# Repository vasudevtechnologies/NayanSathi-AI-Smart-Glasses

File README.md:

# NayanSathi-AI-Smart-Glasses
🕶️ NayanSathi — AI Smart Glasses for the Visually Impaired NayanSathi is an AI-powered wearable assistive system designed to help visually impaired individuals navigate and understand their surroundings in real time. Built using Raspberry Pi 4, ESP32-CAM, YOLOv11, and Edge AI technologies, the smart glasses detect nearby objects

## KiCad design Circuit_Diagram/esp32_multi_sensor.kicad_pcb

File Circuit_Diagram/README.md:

# ⚡ Circuit_Diagram

This folder contains all circuit schematics and PCB design files for **NayanSathi — AI Smart Glasses**.

## Contents
- `esp32_multi_sensor.kicad_pcb` — Main KiCad PCB design
- `schematic.pdf` — Printable full circuit schematic
- `wiring_diagram.png` — Complete wiring connection diagram
- `power_circuit.png` — Solar + battery power circuit
- `pcb_gerber/` — Gerber files for PCB manufacturing

## Power Circuit

```
☀️ Solar Panel (5V, 1W)
         │
         ▼
   ┌─────────────┐
   │   TP4056    │  ← Charge Controller (overcharge protected)
   │   Module    │
   └──────┬──────┘
          │
          ▼
   Li-Po Battery (3.7V, 3000mAh)
          │
          ▼
   ┌─────────────┐
   │   MT3608    │  ← Boost Converter (3.7V → 5V)
   │   Boost     │
   └──────┬──────┘
          │
     ┌────┴────┐
     ▼         ▼
Raspberry Pi 4  ESP32-CAM
  (USB-C 5V)   (5V Pin)
```

## Pin Connections

| From | Pin | To | Pin | Signal |
|---|---|---|---|---|
| ESP32-CAM | GPIO 1 (TX) | Raspberry Pi | GPIO 15 (RX) | UART |
| ESP32-CAM | 5V | MT3608 OUT | 5V | Power |
| ESP32-CAM | GND | Common GND | GND | Ground |
| Solar Panel | + | TP4056 | IN+ | 5V Solar Input |
| Solar Panel | - | TP4056 | IN- | Ground |
| TP4056 | BAT+ | Li-Po | + | Battery Charge |
| Li-Po | + | MT3608 | IN+ | 3.7V Input |
| MT3608 | OUT+ | Pi USB-C | + | 5V Output |
| Voltage Divider | OUT | Pi | GPIO ADC | Battery % |

## PCB Features (KiCad Design)
- ESP32-CAM mounting pads with castellated holes
- TP4056 solar charge controller footprint
- MT3608 boost converter section
- Voltage divider circuit (100kΩ + 100kΩ) for battery ADC monitoring
- I2C header (SDA/SCL) for optional IMU / barometer sensor
- Push button (GPIO 17) for mode switching
- 3x LED indicators: Power (Green), Bluetooth (Blue), Detection (Cyan)
- Magnetic pogo-pin pads for solar panel connector

## PCB Dimensions
- Size: ~45mm × 30mm (fits inside glasses frame)
- Layers: 2-layer PCB
- Thickness: 1.6mm standard FR4

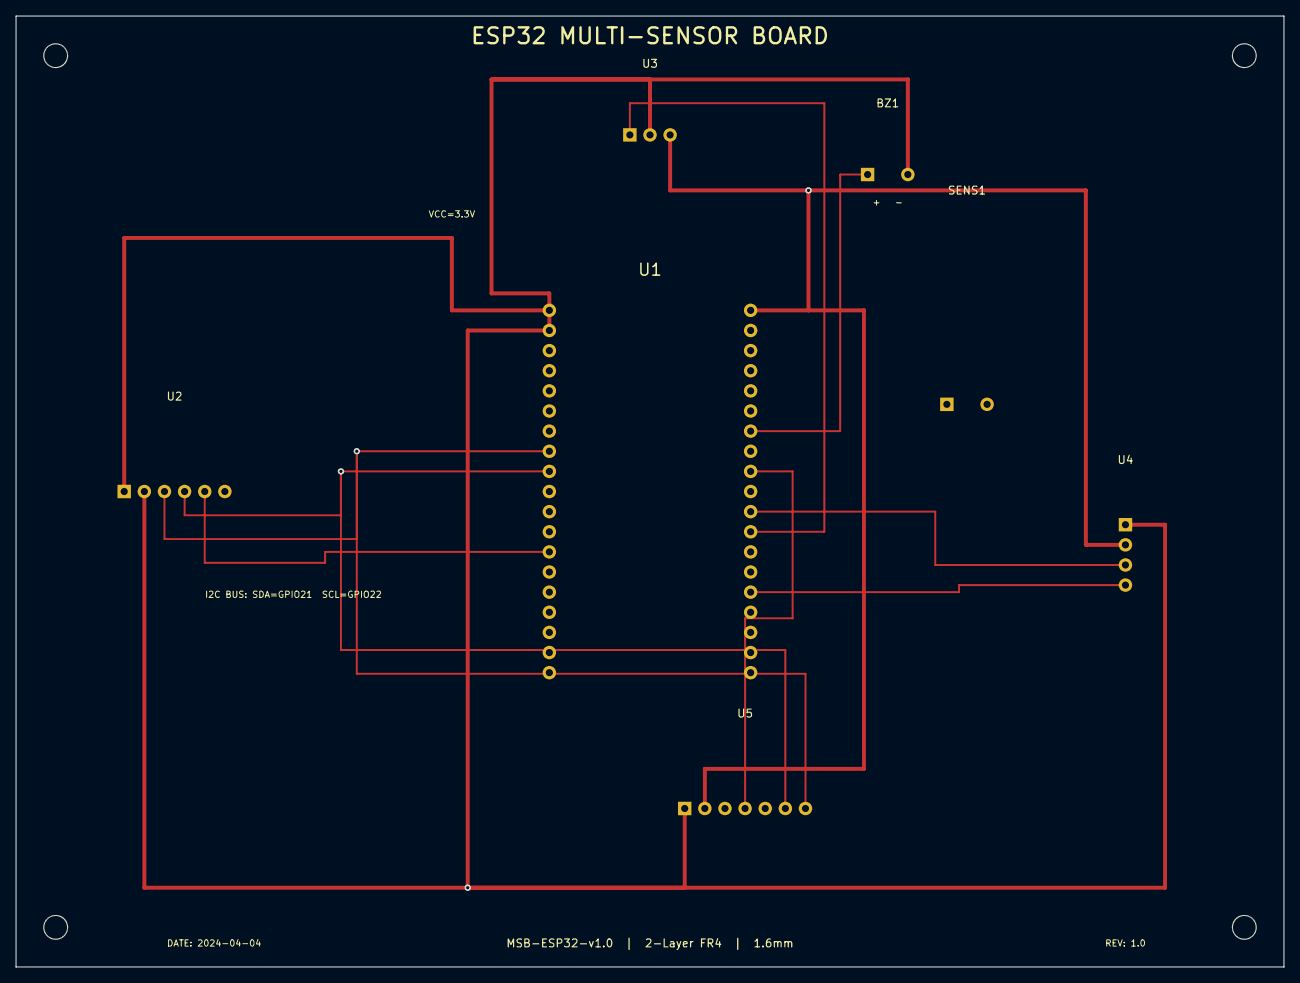
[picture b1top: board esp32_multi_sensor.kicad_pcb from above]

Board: 2 copper layers, 160.0 x 120.0 mm, 7 parts (0 on the bottom side), 10 nets.

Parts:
BZ1: Buzzer-5V; Buzzer_12mm_Vertical
SENS1: Rain-Pad; RainPad
U1: NodeMCU-32S
U2: CJVL53L0XV2; VL53L0X_Module
U3: IR-Sensor; IR_Module_3P
U4: Rain-LM393; RainModule_LM393
U5: ADXL345; ADXL345_Module

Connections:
ADXL_INT1: U1.R9, U5.4
BUZZER_OUT: BZ1.1, U1.R7
GND: BZ1.2, U1.L2, U1.L18, U1.R2, U1.R16, U2.2, U3.2, U4.1, U5.1
I2C_SCL: U1.L8, U2.3, U5.7
I2C_SDA: U1.L9, U2.4, U5.6
IR_OUT: U1.R12, U3.1
RAIN_AO: U1.R15, U4.4
RAIN_DO: U1.R11, U4.3
VCC_3V3: U1.L1, U1.L19, U1.R1, U1.R17, U2.1, U3.3, U4.2, U5.2
XSHUT: U1.L13, U2.5

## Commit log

2026-05-23 Add project folders: Images, Videos, Hardware, Software, Documentation, AI_Model, Circuit_Diagram
2026-05-23 Rename Gemini_Generated_Image_1iou8h1iou8h1iou.png to img1.png
2026-05-23 Rename ChatGPT Image May 23, 2026, 10_36_23 PM.png to new_img.png
2026-05-23 Rename Screenshot 2026-05-23 215126.png to yolo-detection-demo.png
2026-05-23 Rename WhatsApp Image 2026-05-23 at 10.02.23 PM (1).jpeg to smart-glasses-top-view.png
2026-05-23 Rename WhatsApp Image 2026-05-23 at 10.20.24 PM.jpeg to smart-glasses-with-solar-top-view.png
2026-05-23 Rename yolo-detection-demo.png to yolo-detection-person-demo.png
2026-05-23 Rename Screenshot 2026-05-23 215258.png to yolo-detection-banana-demo.png
2026-05-23 Rename Screenshot 2026-05-23 215224.png to yolo-detection-phone+person-demo.png
2026-05-23 Rename Screenshot 2026-05-23 215142.png to yolo-detection-scissor-demo.png
2026-05-23 Rename new_img.png to product.png
2026-05-23 Rename img1.png to hero-banner.png
2026-05-23 Rename ChatGPT Image May 23, 2026, 10_46_18 PM.png to Hardware.png
2026-05-23 Add all code files for Software (pi_scripts, server, esp32, dashboard), AI_Model (YOLOv11n ONNX), and Circuit_Diagram (KiCad PCB)
2026-05-23 Add futuristic NayanSathi website for Vercel deployment — includes hero, features, architecture, dashboard, hardware, circuit, future scope sections with AI-generated images
2026-05-23 feat: add 3D model section, fix icon, fix Vercel image loading
